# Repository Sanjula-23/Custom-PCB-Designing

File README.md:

# Custom-PCB-Designing
PCB Designs using KiCAD

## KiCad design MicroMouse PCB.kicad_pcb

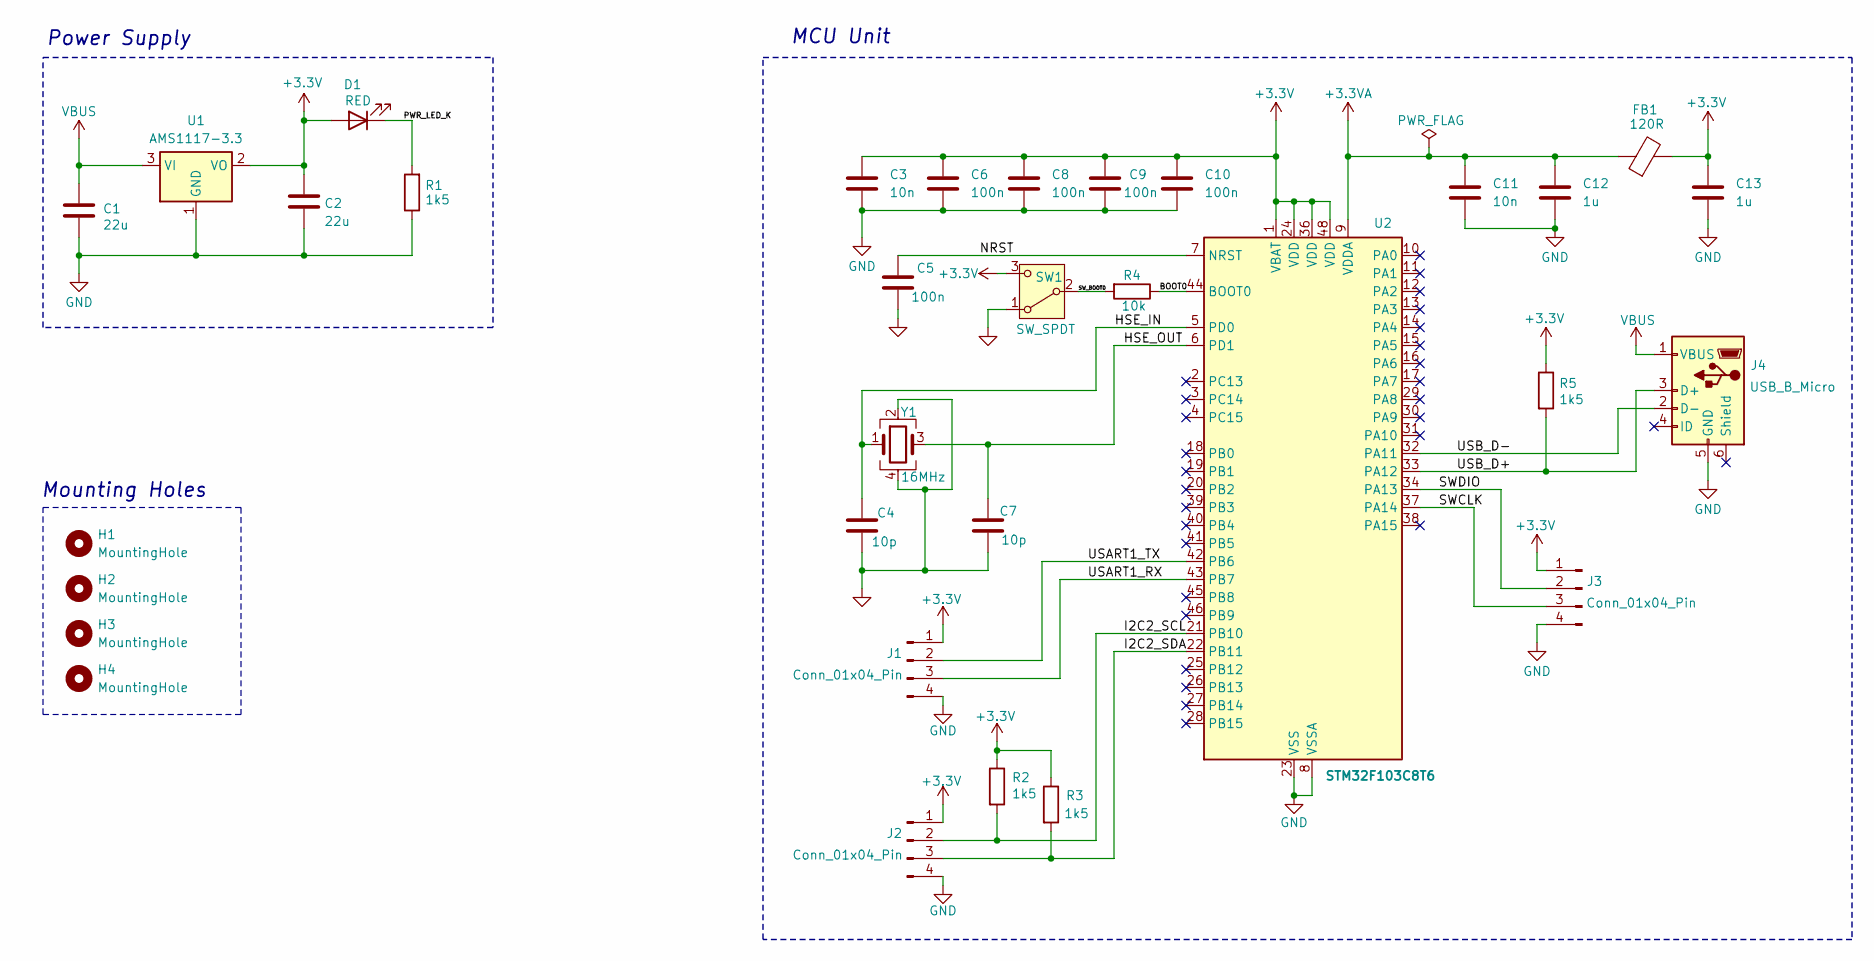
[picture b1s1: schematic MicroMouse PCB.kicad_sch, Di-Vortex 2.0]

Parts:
C1, C2: 22u; C_0805_2012Metric
C3: 10n; C_0603_1608Metric
C4, C7: 10p; C_0402_1005Metric
C5, C6, C8, C9, C10: 100n; C_0402_1005Metric
C11: 10n; C_0402_1005Metric
C12, C13: 1u; C_0402_1005Metric
D1: RED; LED_0603_1608Metric
FB1: 120R; L_0603_1608Metric
H1, H2, H3, H4: MountingHole; MountingHole_2.2mm_M2
J1, J2, J3: Conn_01x04_Pin; PinSocket_1x04_P2.54mm_Vertical
J4: USB_B_Micro; USB_Micro-B_Wuerth_629105150521
R1, R2, R3, R5: 1k5; R_0402_1005Metric
R4: 10k; R_0402_1005Metric
SW1: SW_SPDT; SW_SPDT_PCM12
U1: AMS1117-3.3; SOT-223-3_TabPin2
U2: STM32F103C8T6; LQFP-48_7x7mm_P0.5mm
Y1: 16MHz; Crystal_SMD_3225-4Pin_3.2x2.5mm

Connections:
+3.3V: C2.1, C3.1, C6.1, C8.1, C9.1, C10.1, C13.1, D1.2 (A), FB1.2, J1.1, J2.1, J3.1, R2.1, R3.1, R5.1, SW1.3 (C), U1.2 (VO), U2.1 (VBAT), U2.24 (VDD), U2.36 (VDD), U2.48 (VDD)
+3.3VA: C11.1, C12.1, FB1.1, U2.9 (VDDA)
/BOOT0: R4.1, U2.44 (BOOT0)
/HSE_IN: C4.1, U2.5 (PD0), Y1.1
/HSE_OUT: C7.1, U2.6 (PD1), Y1.3
/I2C2_SCL: J2.2, R2.2, U2.21 (PB10)
/I2C2_SDA: J2.3, R3.2, U2.22 (PB11)
/NRST: C5.1, U2.7 (NRST)
/PWR_LED_K: D1.1 (K), R1.2
/SWCLK: J3.3, U2.37 (PA14)
/SWDIO: J3.2, U2.34 (PA13)
/SW_BOOT0: R4.2, SW1.2 (B)
/USART1_RX: J1.3, U2.43 (PB7)
/USART1_TX: J1.2, U2.42 (PB6)
/USB_D+: J4.3 (D+), R5.2, U2.33 (PA12)
/USB_D-: J4.2 (D-), U2.32 (PA11)
GND: C1.2, C2.2, C3.2, C4.2, C5.2, C6.2, C7.2, C8.2, C9.2, C10.2, C11.2, C12.2, C13.2, J1.4, J2.4, J3.4, J4.5 (GND), R1.1, SW1.1 (A), U1.1 (GND), U2.8 (VSSA), U2.23 (VSS), U2.35 (VSS), U2.47 (VSS), Y1.2, Y1.4
VBUS: C1.1, J4.1 (VBUS), U1.3 (VI)

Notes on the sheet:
MCU Unit
Power Supply
Mounting Holes

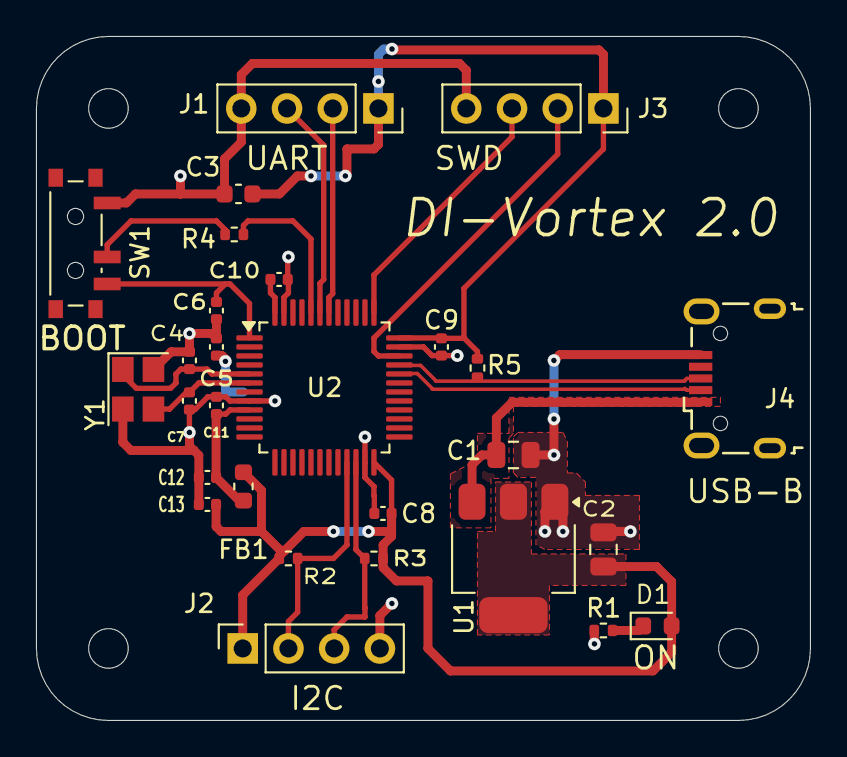
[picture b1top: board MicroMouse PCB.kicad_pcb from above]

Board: 2 copper layers, 43.0 x 38.0 mm, 32 parts (0 on the bottom side), 18 nets.

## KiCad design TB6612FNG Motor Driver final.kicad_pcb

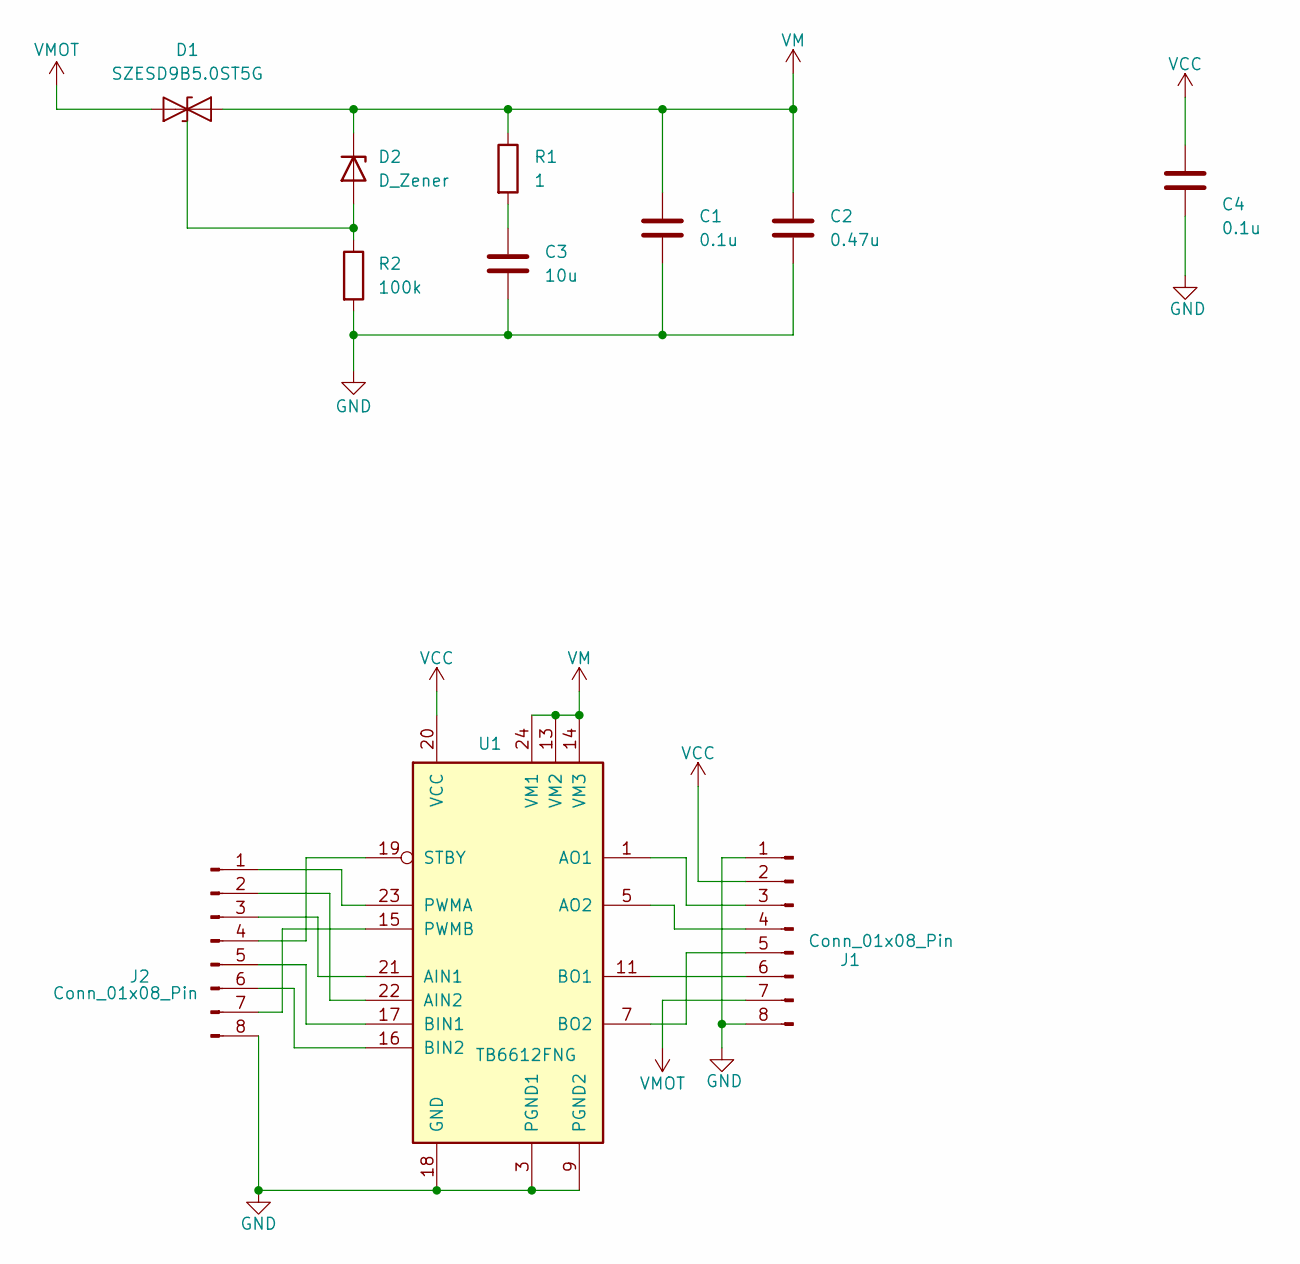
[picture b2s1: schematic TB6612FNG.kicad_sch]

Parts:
C1, C4: 0.1u; C_0603_1608Metric_Pad1.08x0.95mm_HandSolder
C2: 0.47u; C_0805_2012Metric_Pad1.18x1.45mm_HandSolder
C3: 10u; C_0805_2012Metric_Pad1.18x1.45mm_HandSolder
D1: SZESD9B5.0ST5G; D_SOD-923
D2: D_Zener; D_0805_2012Metric_Pad1.15x1.40mm_HandSolder
J1, J2: Conn_01x08_Pin; Harwin_M20-89008xx_1x08_P2.54mm_Horizontal
R1: 1; R_0805_2012Metric
R2: 100k; R_0805_2012Metric
U1: TB6612FNG; SSOP-24_5.3x8.2mm_P0.65mm

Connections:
/A01: J1.3, U1.1 (AO1), U1.2 (AO1)
/A02: J1.4, U1.5 (AO2), U1.6 (AO2)
/AIN1: J2.3, U1.21 (AIN1)
/AIN2: J2.2, U1.22 (AIN2)
/B01: J1.6, U1.11 (BO1), U1.12 (BO1)
/B02: J1.5, U1.7 (BO2), U1.8 (BO2)
/BIN1: J2.5, U1.17 (BIN1)
/BIN2: J2.6, U1.16 (BIN2)
/PWMA: J2.1, U1.23 (PWMA)
/PWMB: J2.7, U1.15 (PWMB)
/STBY: J2.4, U1.19 (STBY)
GND: C1.2, C2.2, C3.2, C4.2, J1.1, J1.8, J2.8, R2.2, U1.3 (PGND1), U1.4 (PGND1), U1.9 (PGND2), U1.10 (PGND2), U1.18 (GND)
unnamed: C3.1, R1.2
unnamed: D2.2 (A), R2.1
VCC: C4.1, J1.2, U1.20 (VCC)
VM: C1.1, C2.1, D1.2 (A2), D2.1 (K), R1.1, U1.13 (VM2), U1.14 (VM3), U1.24 (VM1)
VMOT: D1.1 (A1), J1.7

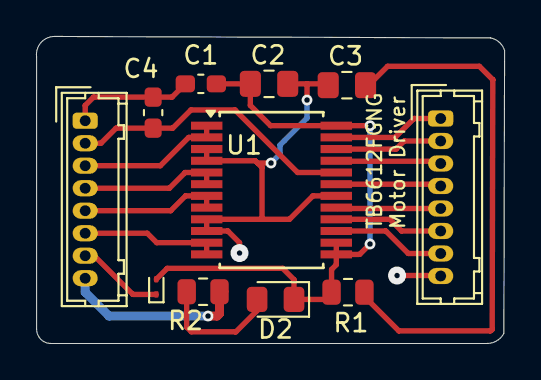
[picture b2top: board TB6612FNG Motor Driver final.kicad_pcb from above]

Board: 2 copper layers, 26.0 x 17.1 mm, 11 parts (0 on the bottom side), 17 nets.

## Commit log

2025-05-27 upload
